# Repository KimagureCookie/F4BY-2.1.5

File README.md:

# F4BY-2.1.5 Fligh controller 

The design files are based on eagle schematics from the Ardupilot repository.

[Ardupilot_Schematics](https://github.com/ArduPilot/Schematics/tree/master/F4BY).

Please do note that the pcb is not tested and was designed as part of an assignment.

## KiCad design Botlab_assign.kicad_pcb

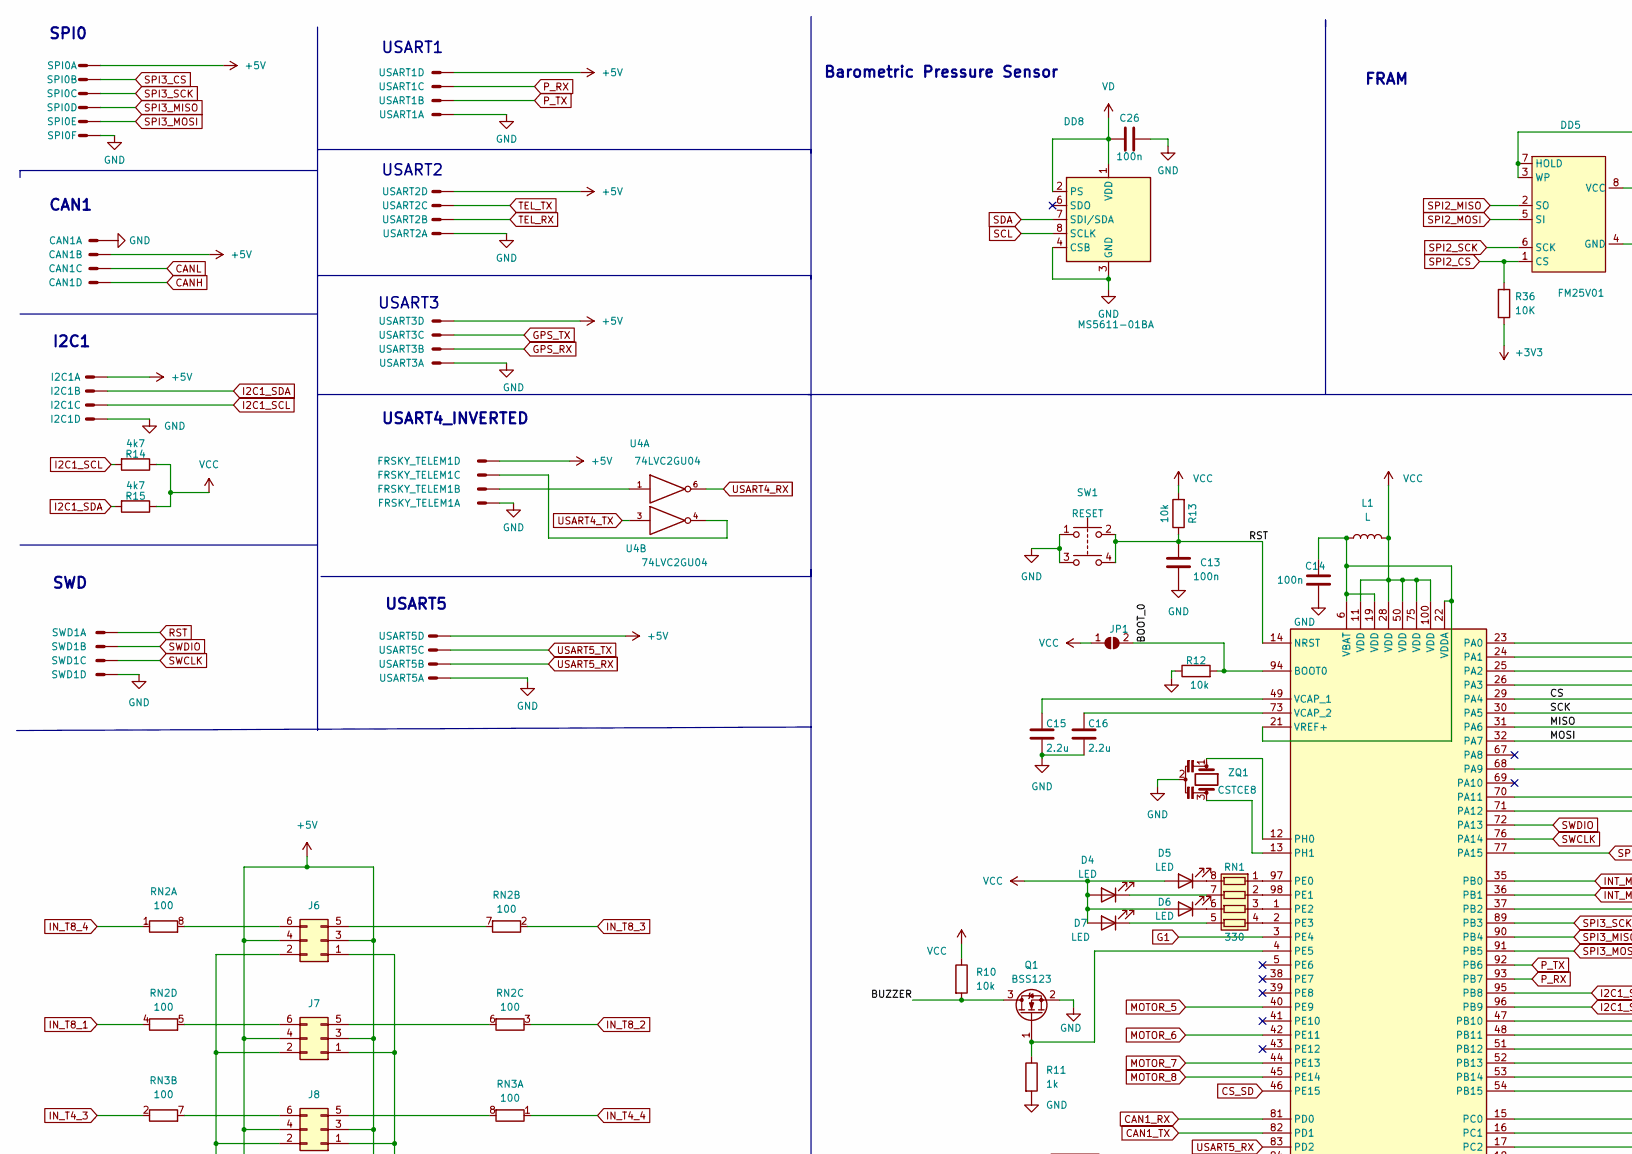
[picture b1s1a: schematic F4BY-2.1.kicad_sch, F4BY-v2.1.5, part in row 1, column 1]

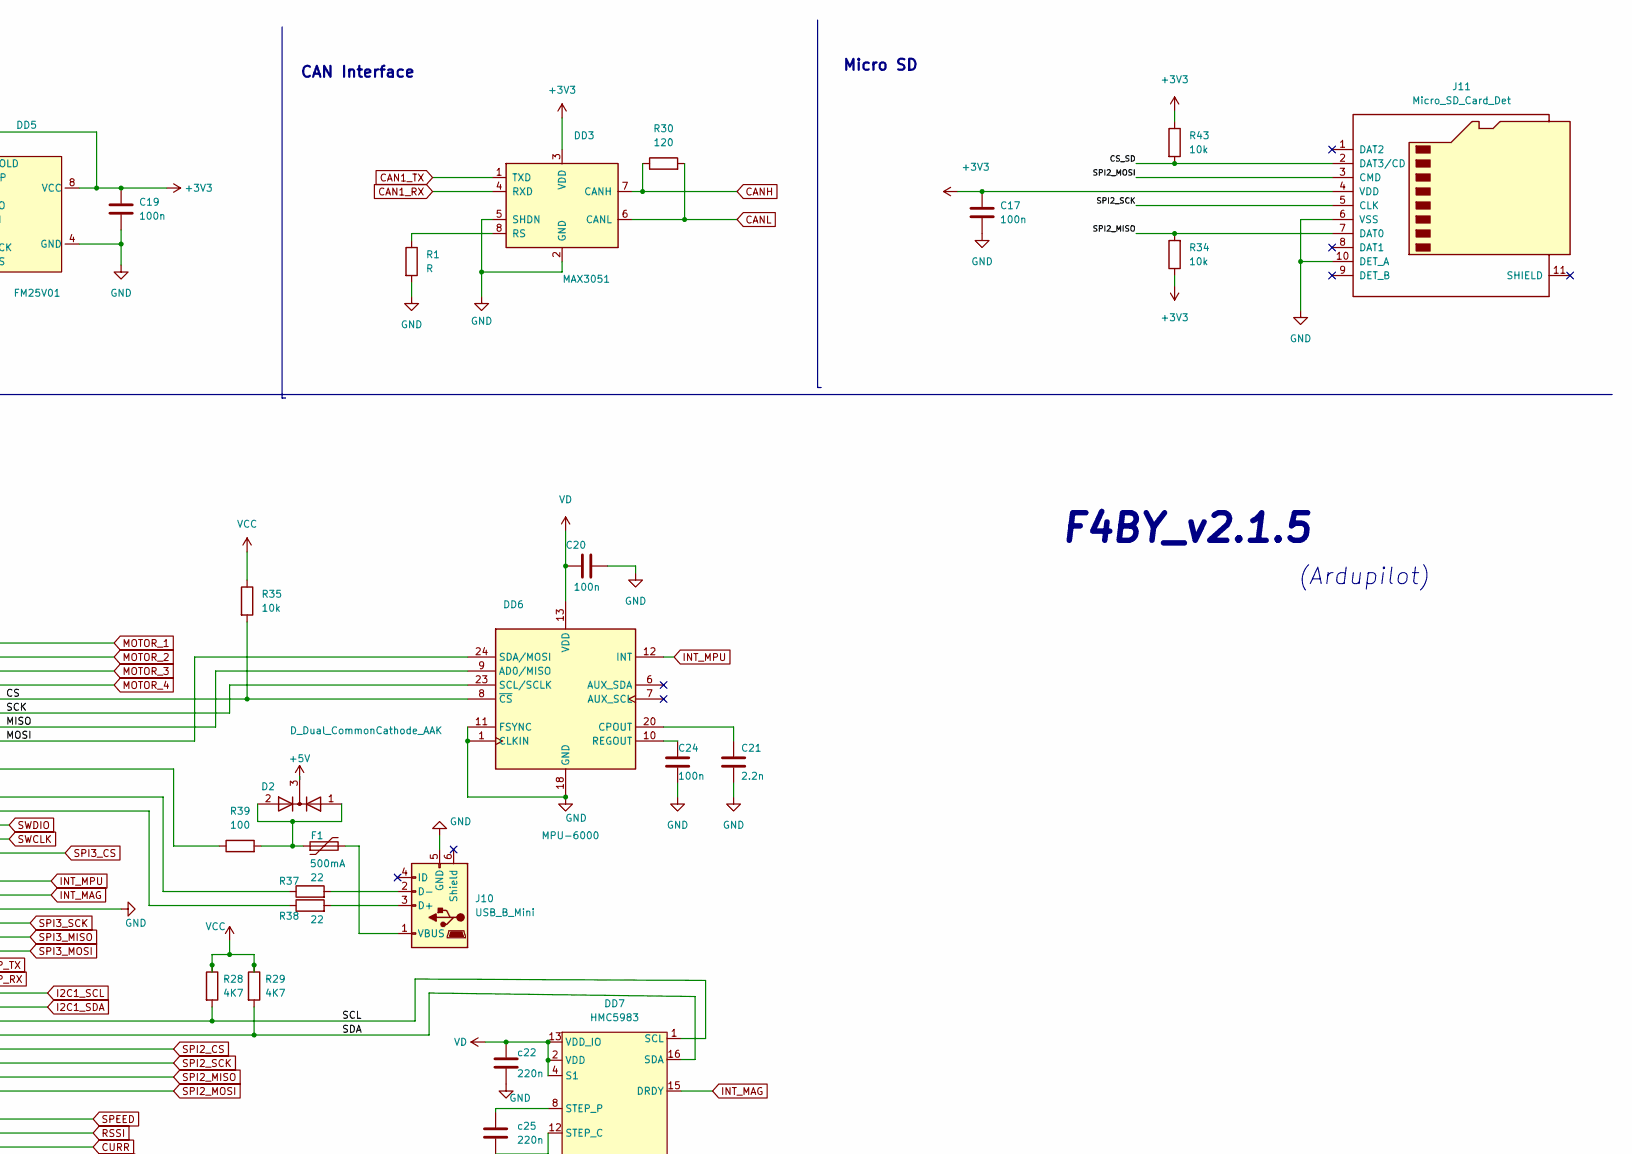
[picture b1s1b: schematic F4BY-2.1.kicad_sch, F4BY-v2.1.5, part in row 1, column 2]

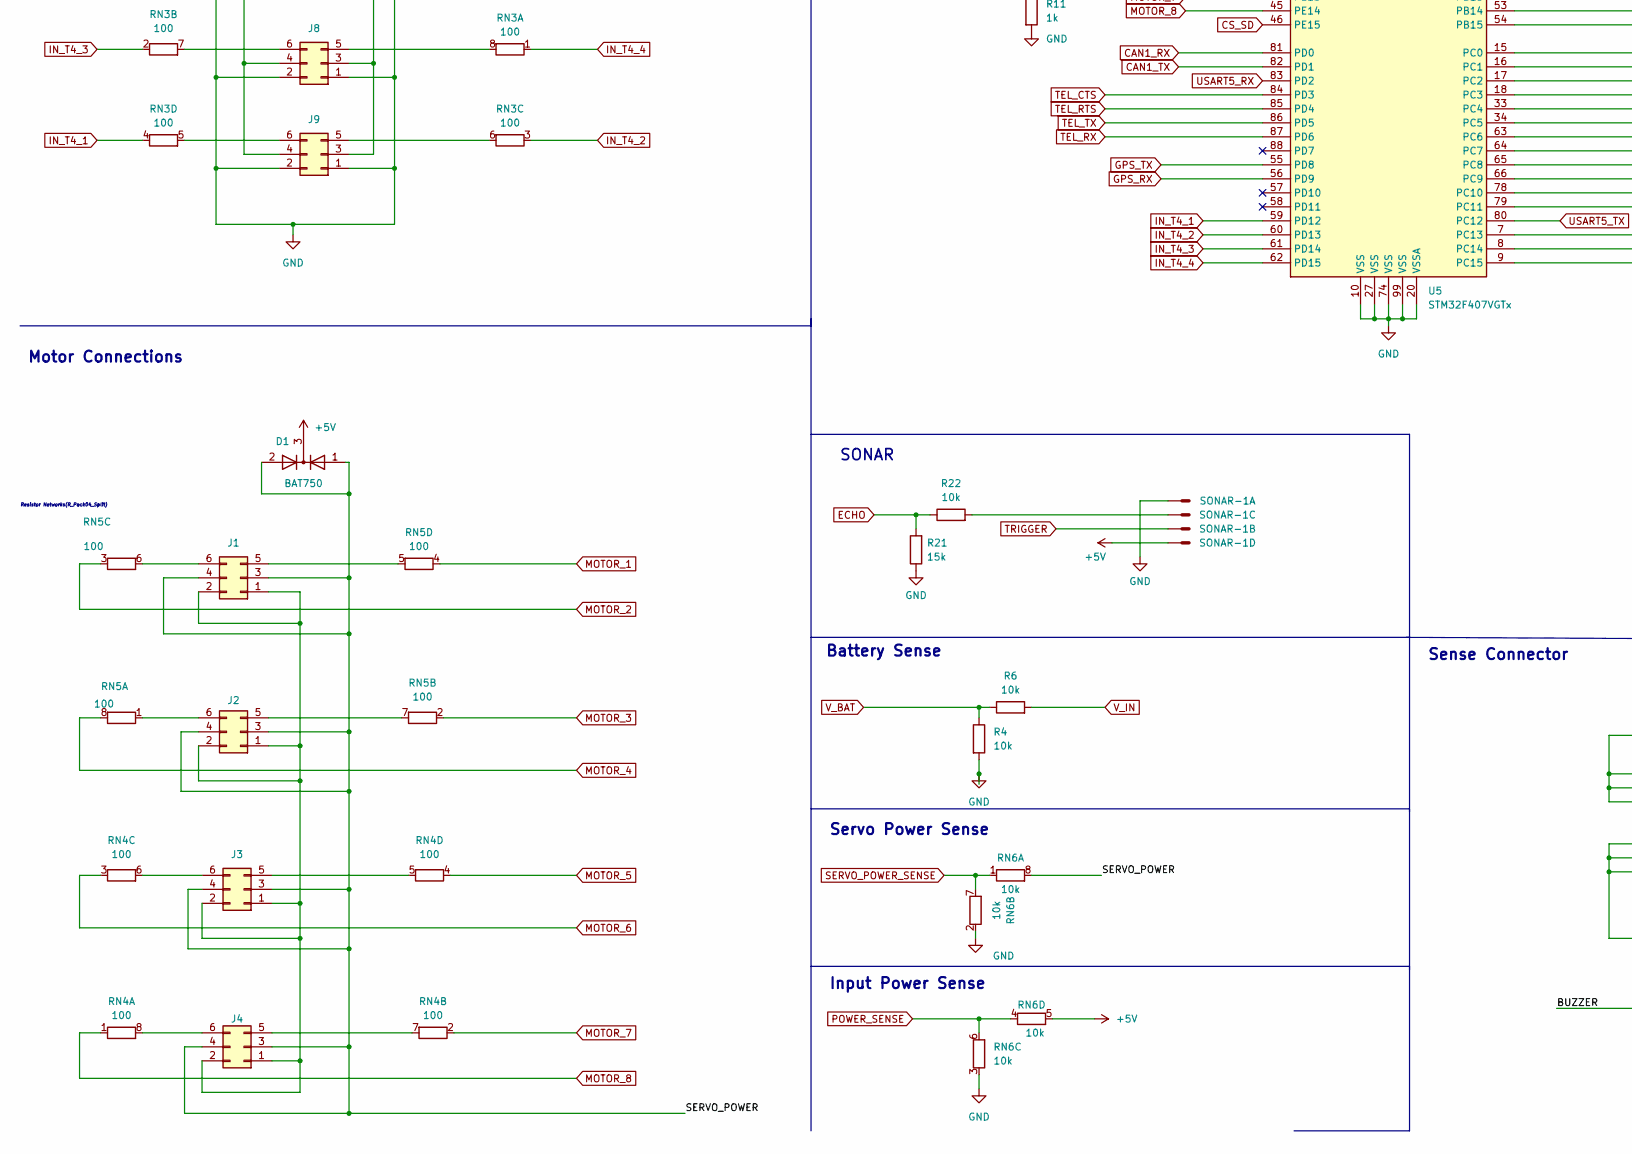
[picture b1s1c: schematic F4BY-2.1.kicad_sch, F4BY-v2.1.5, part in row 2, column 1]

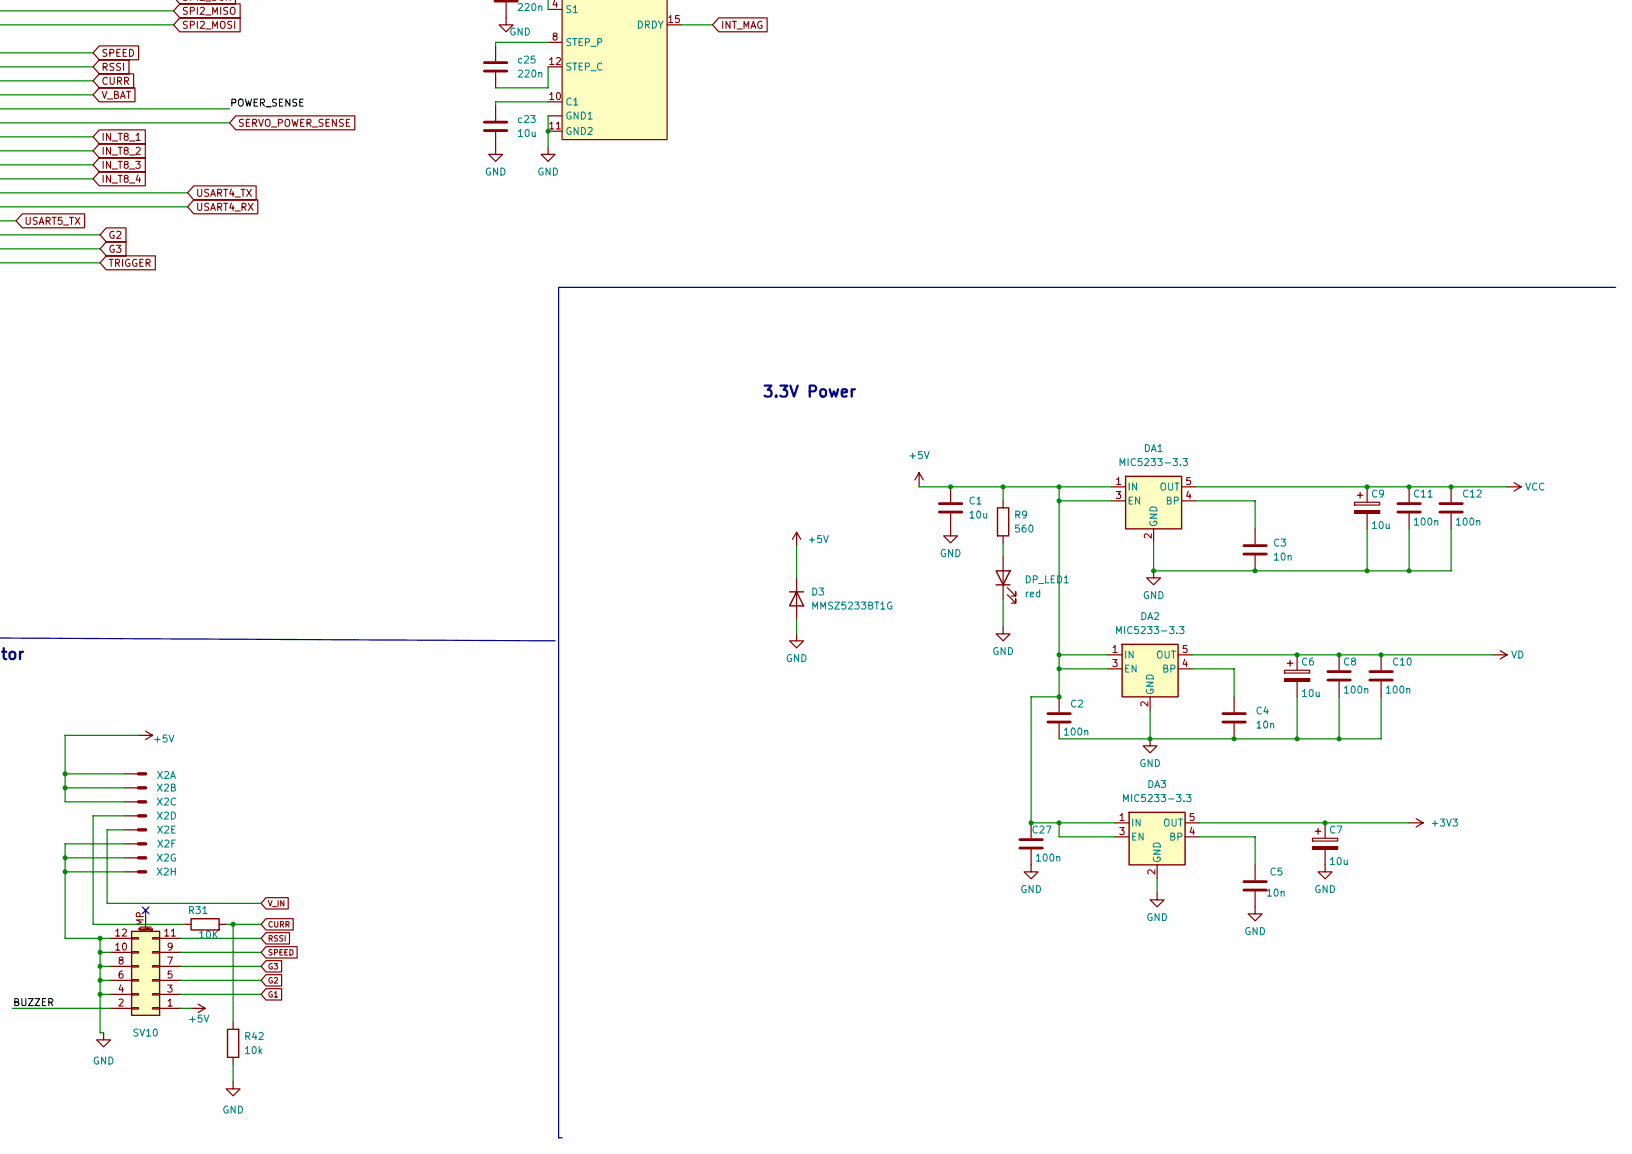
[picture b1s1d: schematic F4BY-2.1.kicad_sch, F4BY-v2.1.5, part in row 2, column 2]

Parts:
C1, C6, C7, C9: 10u
C2, C8, C10, C11, C12, C13, C14, C17, C19, C20, C24, C26, C27: 100n
C3, C4, C5: 10n
C15, C16: 2.2u
C21: 2.2n
CAN1: ?M04B-SRSS-TBS_1
D1: BAT750
D2: D_Dual_CommonCathode_AAK
D3: MMSZ5233BT1G; D_SOD-123
D4, D5, D6, D7: LED
DA1, DA2, DA3: MIC5233-3.3; SOT-23-5
DD3: MAX3051
DD5: FM25V01
DD6: MPU-6000; InvenSense_QFN-24_4x4mm_P0.5mm
DD7: HMC5983
DD8: MS5611-01BA; LGA-8_3x5mm_P1.25mm
DP_LED1: red
F1: 500mA
FRSKY_TELEM1: ?M04B-SRSS-TBS_1
I2C1: ?M04B-SRSS-TBS_1
J1, J2, J3, J4, J6, J7, J8, J9: Conn_02x03_Odd_Even
J10: USB_B_Mini
J11: Micro_SD_Card_Det
JP1: SolderJumper_2_Open
L1: L
Q1: BSS123; SOT-23
R1: R
R4, R6, R10, R12, R13, R22, R34, R35, R42, R43: 10k
R9: 560
R11: 1k
R14, R15: 4k7
R21: 15k
R28, R29: 4K7
R30: 120
R31, R36: 10K
R37, R38: 22
R39: 100
RN1: 330
RN2, RN3, RN4, RN5: 100
RN6: 10k
SONAR-1: ?M04B-SRSS-TBS_1
SPI0: M06B-SRSS-TBS
SV10: Conn_02x06_Odd_Even_MountingPin
SW1: RESET
SWD1: ?M04B-SRSS-TBS_1
U4: 74LVC2GU04
U5: STM32F407VGTx; LQFP-100_14x14mm_P0.5mm
USART1, USART2, USART3, USART5: ?M04B-SRSS-TBS_1
X2: ?M08B-SRSS-TBS
ZQ1: CSTCE8
c22, c25: 220n
c23: 10u

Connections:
+3V3: C7.1, C17.1, C19.1, DA3.5 (OUT), DD3.3 (VDD), DD5.3 (WP), DD5.7 (HOLD), DD5.8 (VCC), J11.4 (VDD), R34.1, R36.2, R43.1
+5V: C1.1, C2.1, C27.1, CAN1.2 (S), D1.3 (K), D2.3 (K), D3.1 (K), DA1.1 (IN), DA1.3 (EN), DA2.1 (IN), DA2.3 (EN), DA3.1 (IN), DA3.3 (EN), FRSKY_TELEM1.4 (S), I2C1.1 (S), J6.3, J6.4, J7.3, J7.4, J8.3, J8.4, J9.3, J9.4, R9.1, RN6.5 (R4.2), SONAR-1.4, SPI0.1 (S), SV10.1, USART1.4 (S), USART2.4 (S), USART3.4 (S), USART5.4 (S), X2.1 (S), X2.2 (S), X2.3 (S); also elsewhere on the board
/BOOT_0: JP1.2 (B), R12.2, U5.94 (BOOT0)
/BUZZER: Q1.3 (D), R10.2, SV10.2
/CS: DD6.8 (~CS), R35.2, U5.29 (PA4)
/D+: R38.1, U5.71 (PA12)
/D-: R37.1, U5.70 (PA11)
/MISO: DD6.9 (AD0/MISO), U5.31 (PA6)
/MOSI: DD6.24 (SDA/MOSI), U5.32 (PA7)
/SCK: DD6.23 (SCL/SCLK), U5.30 (PA5)
/SERVO_POWER: D1.1 (A), D1.2 (A), J1.3, J1.4, J2.3, J2.4, J3.3, J3.4, J4.3, J4.4, RN6.8 (R1.2)
CAN1_RX: DD3.4 (RXD), U5.81 (PD0)
CAN1_TX: DD3.1 (TXD), U5.82 (PD1)
CANH: CAN1.4 (S), DD3.7 (CANH), R30.1
CANL: CAN1.3 (S), DD3.6 (CANL), R30.2
CS_SD: J11.2 (DAT3/CD), R43.2, U5.46 (PE15)
CURR: R31.2, R42.2, U5.17 (PC2)
ECHO: R21.2, R22.1, U5.5 (PE6)
G1: SV10.3, U5.3 (PE4)
G2: SV10.5, U5.7 (PC13)
G3: SV10.7, U5.8 (PC14)
GND: C1.2, C2.2, C3.2, C4.2, C5.2, C6.2, C7.2, C8.2, C9.2, C10.2, C11.2, C12.2, C13.2, C14.1, C15.2, C16.2, C17.2, C19.2, C20.2, C21.2, C24.2, C26.1, C27.2, CAN1.1 (S), D3.2 (A), DA1.2 (GND), DA2.2 (GND), DA3.2 (GND), DD3.2 (GND), DD3.5 (SHDN), DD5.4 (GND), DD6.1 (CLKIN), DD6.11 (FSYNC), DD6.18 (GND), DD7. (GND1), DD7.11 (GND2), DD8.3 (GND), DD8.4 (CSB), DD8.5 (CSB), DP_LED1.1 (K), FRSKY_TELEM1.1 (S), I2C1.4 (S), J6.1, J6.2, J7.1, J7.2, J8.1, J8.2, J9.1, J9.2, J10.5 (GND), J11.6 (VSS), J11.10 (DET_A), Q1.2 (S), R1.2, R4.2, R11.2, R12.1, R21.1, R42.1, RN6.2 (R2.1), RN6.3 (R3.1), SONAR-1.1, SPI0.6 (S), SV10.4, SV10.6, SV10.8, SV10.10, SV10.12, SW1.1, SW1.3, SWD1.4 (S), U4.2 (GND), U5.10 (VSS), U5.20 (VSSA), U5.27 (VSS), U5.37 (PB2), U5.74 (VSS), U5.99 (VSS), USART1.1 (S), USART2.1 (S), USART3.1 (S), USART5.1 (S), X2.6 (S), X2.7 (S), X2.8 (S), ZQ1.2, c22.2, c23.2; also elsewhere on the board
GPS_RX: U5.56 (PD9), USART3.2 (S)
GPS_TX: U5.55 (PD8), USART3.3 (S)
I2C1_SCL: I2C1.3 (S), R14.2, U5.95 (PB8)
I2C1_SDA: I2C1.2 (S), R15.2, U5.96 (PB9)
INT_MAG: DD7.15 (DRDY), U5.36 (PB1)
INT_MPU: DD6.12 (INT), U5.35 (PB0)
IN_T4_1: RN3.4 (R4.1), U5.59 (PD12)
IN_T4_2: RN3.3 (R3.1), U5.60 (PD13)
IN_T4_3: RN3.2 (R2.1), U5.61 (PD14)
IN_T4_4: RN3.1 (R1.1), U5.62 (PD15)
IN_T8_1: RN2.4 (R4.1), U5.63 (PC6)
IN_T8_2: RN2.3 (R3.1), U5.64 (PC7)
IN_T8_3: RN2.2 (R2.1), U5.65 (PC8)
IN_T8_4: RN2.1 (R1.1), U5.66 (PC9)
MOTOR_1: RN5.4 (R4.1), U5.23 (PA0)
MOTOR_2: RN5.3 (R3.1), U5.24 (PA1)
MOTOR_3: RN5.2 (R2.1), U5.25 (PA2)
MOTOR_4: RN5.8 (R1.2), U5.26 (PA3)
MOTOR_5: RN4.4 (R4.1), U5.40 (PE9)
MOTOR_6: RN4.3 (R3.1), U5.42 (PE11)
MOTOR_7: RN4.2 (R2.1), U5.44 (PE13)
MOTOR_8: RN4.1 (R1.1), U5.45 (PE14)
unnamed: C3.1, DA1.4 (BP)
unnamed: C4.1, DA2.4 (BP)
unnamed: C5.1, DA3.4 (BP)
unnamed 47: C14.2, L1.1, U5.6 (VBAT), U5.19 (VDD), U5.21 (VREF+), U5.22 (VDDA); also elsewhere on the board
unnamed: C15.1, U5.49 (VCAP_1)
unnamed: C16.1, U5.73 (VCAP_2)
unnamed: C21.1, DD6.20 (CPOUT)
unnamed: C24.1, DD6.10 (REGOUT)
unnamed: D2.1 (A), D2.2 (A), F1.1, R39.2
unnamed: D4.1 (K), RN1.7 (R2.2)
unnamed: D5.1 (K), RN1.8 (R1.2)
unnamed: D6.1 (K), RN1.6 (R3.2)
unnamed: D7.1 (K), RN1.5 (R4.2)
unnamed: DD3.8 (RS), R1.1
unnamed: DD7.8 (STEP_P), c25.1
unnamed: DD7.10 (C1), c23.1
unnamed: DD7.12 (STEP_C), c25.2
unnamed: DP_LED1.2 (A), R9.2
unnamed: F1.2, J10.1 (VBUS)
unnamed: FRSKY_TELEM1.2 (S), U4.1
unnamed: FRSKY_TELEM1.3 (S), U4.4
unnamed: J1.1, J1.2, J2.1, J2.2, J3.1, J3.2, J4.1, J4.2
unnamed: J1.5, RN5.5 (R4.2)
unnamed: J1.6, RN5.6 (R3.2)
unnamed: J2.5, RN5.7 (R2.2)
unnamed: J2.6, RN5.1 (R1.1)
unnamed: J3.5, RN4.5 (R4.2)
unnamed: J3.6, RN4.6 (R3.2)
unnamed: J4.5, RN4.7 (R2.2)
unnamed: J4.6, RN4.8 (R1.2)
unnamed: J6.5, RN2.7 (R2.2)
unnamed: J6.6, RN2.8 (R1.2)
unnamed: J7.5, RN2.6 (R3.2)
unnamed: J7.6, RN2.5 (R4.2)
unnamed: J8.5, RN3.8 (R1.2)
unnamed: J8.6, RN3.7 (R2.2)
unnamed: J9.5, RN3.6 (R3.2)
unnamed: J9.6, RN3.5 (R4.2)
unnamed: J10.2 (D-), R37.2
unnamed: J10.3 (D+), R38.2
unnamed: Q1.1 (G), R11.1, U5.4 (PE5)
unnamed 85: R22.2, SONAR-1.3; also elsewhere on the board
unnamed: R31.1, X2.4 (S)
unnamed: R39.1, U5.68 (PA9)
unnamed: RN1.1 (R1.1), U5.97 (PE0)
unnamed: RN1.2 (R2.1), U5.98 (PE1)
unnamed: RN1.3 (R3.1), U5.1 (PE2)
unnamed: RN1.4 (R4.1), U5.2 (PE3)
unnamed: U5.12 (PH0), ZQ1.1
unnamed: U5.13 (PH1), ZQ1.3
POWER_SENSE: RN6.4 (R4.1), RN6.6 (R3.2), U5.33 (PC4)
P_RX: U5.93 (PB7), USART1.3 (S)
P_TX: U5.92 (PB6), USART1.2 (S)
RSSI: SV10.11, U5.16 (PC1)
RST: C13.1, R13.1, SW1.2, SW1.4, SWD1.1 (S), U5.14 (NRST)
SCL: DD7.1 (SCL), DD8.8 (SCLK), R28.2, U5.47 (PB10)
SDA: DD7.16 (SDA), DD8.7 (SDI/SDA), R29.2, U5.48 (PB11)
SERVO_POWER_SENSE: RN6.1 (R1.1), RN6.7 (R2.2), U5.34 (PC5)
SPEED: SV10.9, U5.15 (PC0)
SPI2_CS: DD5.1 (CS), R36.1, U5.51 (PB12)
SPI2_MISO: DD5.2 (SO), J11.7 (DAT0), R34.2, U5.53 (PB14)
SPI2_MOSI: DD5.5 (SI), J11.3 (CMD), U5.54 (PB15)
SPI2_SCK: DD5.6 (SCK), J11.5 (CLK), U5.52 (PB13)
SPI3_CS: SPI0.2 (S), U5.77 (PA15)
SPI3_MISO: SPI0.4 (S), U5.90 (PB4)
SPI3_MOSI: SPI0.5 (S), U5.91 (PB5)
SPI3_SCK: SPI0.3 (S), U5.89 (PB3)
SWCLK: SWD1.3 (S), U5.76 (PA14)
SWDIO: SWD1.2 (S), U5.72 (PA13)
TEL_CTS: U5.84 (PD3)
TEL_RTS: U5.85 (PD4)
TEL_RX: U5.87 (PD6), USART2.2 (S)
TEL_TX: U5.86 (PD5), USART2.3 (S)
TRIGGER: SONAR-1.2, U5.9 (PC15); also elsewhere on the board
USART4_RX: U4.6, U5.79 (PC11)
USART4_TX: U4.3, U5.78 (PC10)
USART5_RX: U5.83 (PD2), USART5.2 (S)
USART5_TX: U5.80 (PC12), USART5.3 (S)
VCC: C9.1, C11.1, C12.1, D4.2 (A), D5.2 (A), D6.2 (A), D7.2 (A), DA1.5 (OUT), JP1.1 (A), L1.2, R10.1, R13.2, R14.1, R15.1, R28.1, R29.1, R35.1, U4.5 (VCC), U5.11 (VDD), U5.28 (VDD), U5.50 (VDD), U5.75 (VDD), U5.100 (VDD); also elsewhere on the board
VD: C6.1, C8.1, C10.1, C20.1, C26.2, DA2.5 (OUT), DD6.13 (VDD), DD7.2 (VDD), DD7.4 (S1), DD7.13 (VDD_IO), DD8.1 (VDD), DD8.2 (PS), c22.1
V_BAT: R4.1, R6.1, U5.18 (PC3)
V_IN: R6.2, X2.5 (S)

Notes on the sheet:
Resistor Networks(R_Pack04_Split)
(Ardupilot)
F4BY_v2.1.5
Servo Power Sense
SWD
SPI0
Barometric Pressure Sensor
SONAR
CAN Interface
I2C1
Sense Connector
USART5
USART1
Micro SD
Motor Connections
USART3
Battery Sense
USART2
Input Power Sense
CAN1
USART4_INVERTED
3.3V Power
FRAM

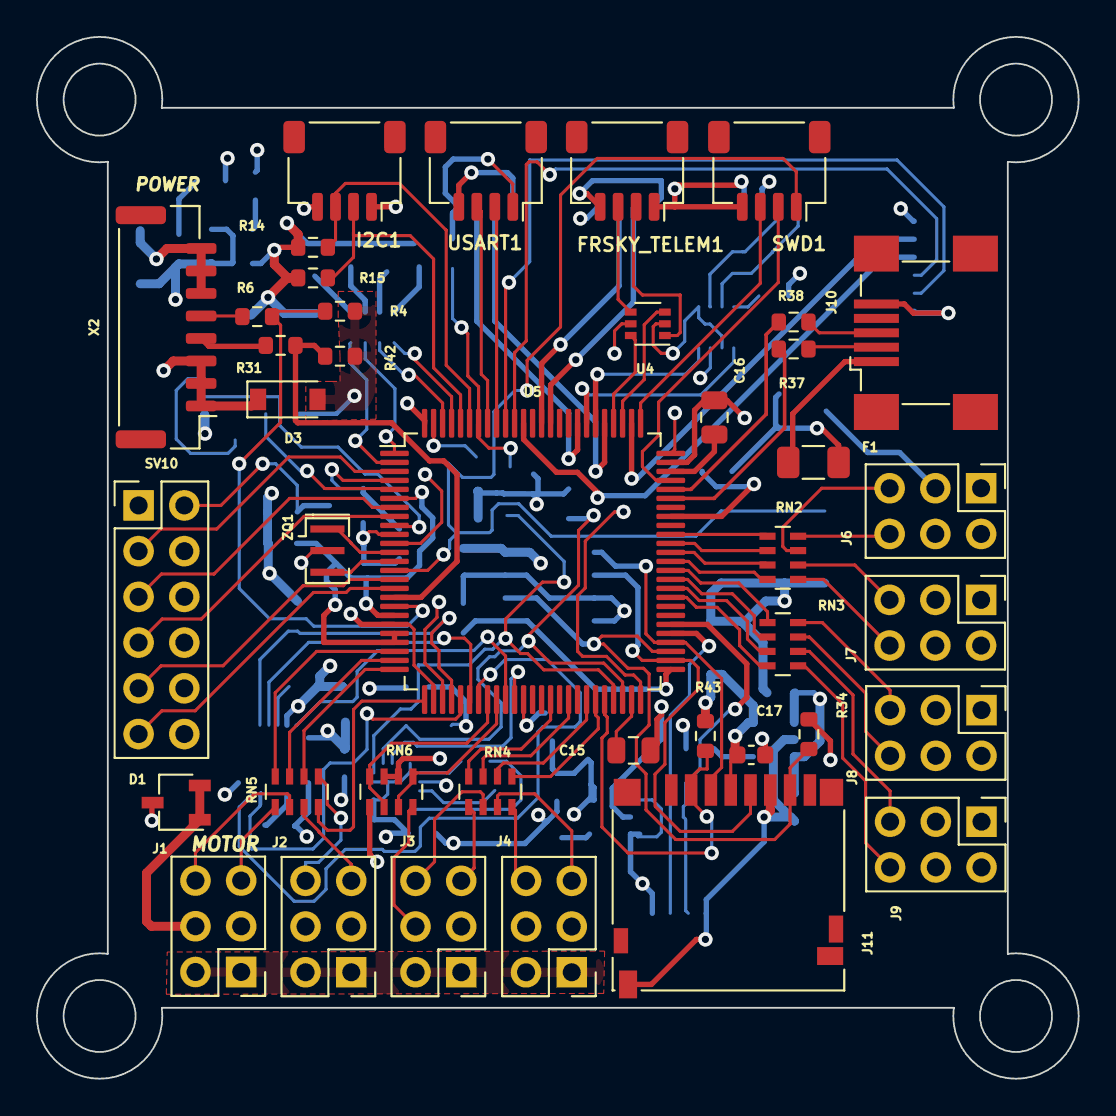
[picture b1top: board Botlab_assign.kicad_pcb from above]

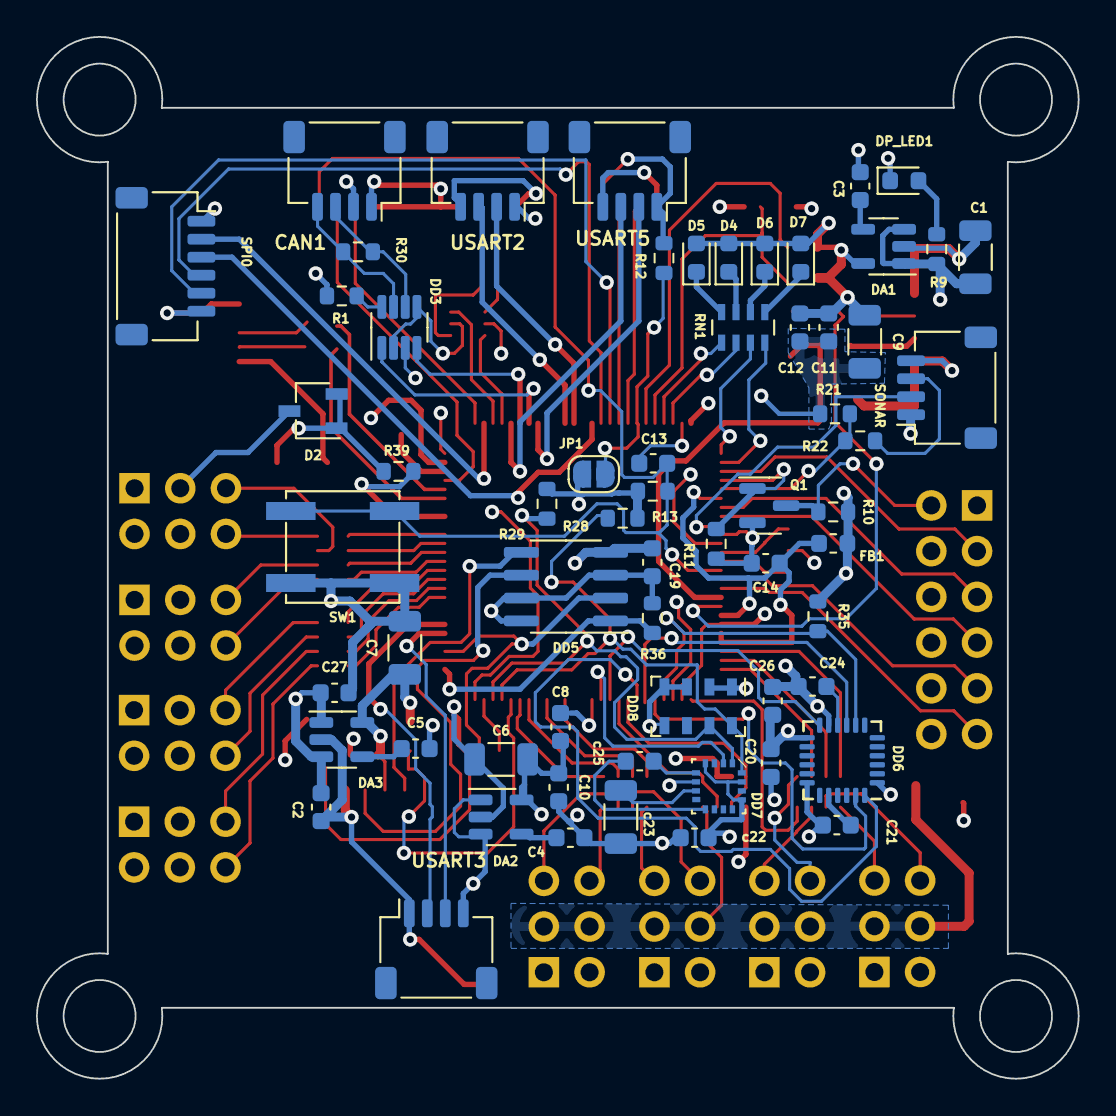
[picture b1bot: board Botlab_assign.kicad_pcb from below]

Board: 4 copper layers, 57.9 x 57.9 mm, 102 parts (62 on the bottom side), 124 nets.

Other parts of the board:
FB1: 120; L_0603_1608Metric
SONAR: ?M04B-SRSS-TBS_1; JST_SH_SM04B-SRSS-TB_1x04-1MP_P1.00mm_Horizontal

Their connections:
+5V: SONAR.4 (S); also elsewhere on the board
GND: SONAR.1 (S); also elsewhere on the board
unnamed 47: FB1.1; also elsewhere on the board
unnamed 85: SONAR.3 (S); also elsewhere on the board
TRIGGER: SONAR.2 (S); also elsewhere on the board
VCC: FB1.2; also elsewhere on the board

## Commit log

2023-05-22 schematic and pdf added
2023-05-22 lib added
2023-06-03 pcb design added
